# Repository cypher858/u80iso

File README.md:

# u80iso
tryna make a rama u80-a iso compatible. wish me luck.

LibreCAD was used to make the plate file

Started in KiCad 5.1.10, now in KiCad 7

I've been following the ai03 pcb design tutorial here https://wiki.ai03.com/books/pcb-design/chapter/pcb-designer-guide

currently in guide step 5 on building the pcb
https://wiki.ai03.com/books/pcb-design/page/pcb-guide-part-5---creating-the-pcb

in placing the controller and other circuit parts into the completed switch matrix, i noticed that what should be GND pins are reading as 5v instead. Bug? looking for feedback on this.

todo:
* fix above bug
* place jst connector footprint on the circuitboard
* tracing circuits
* silk screening for fun
* more? is there more?

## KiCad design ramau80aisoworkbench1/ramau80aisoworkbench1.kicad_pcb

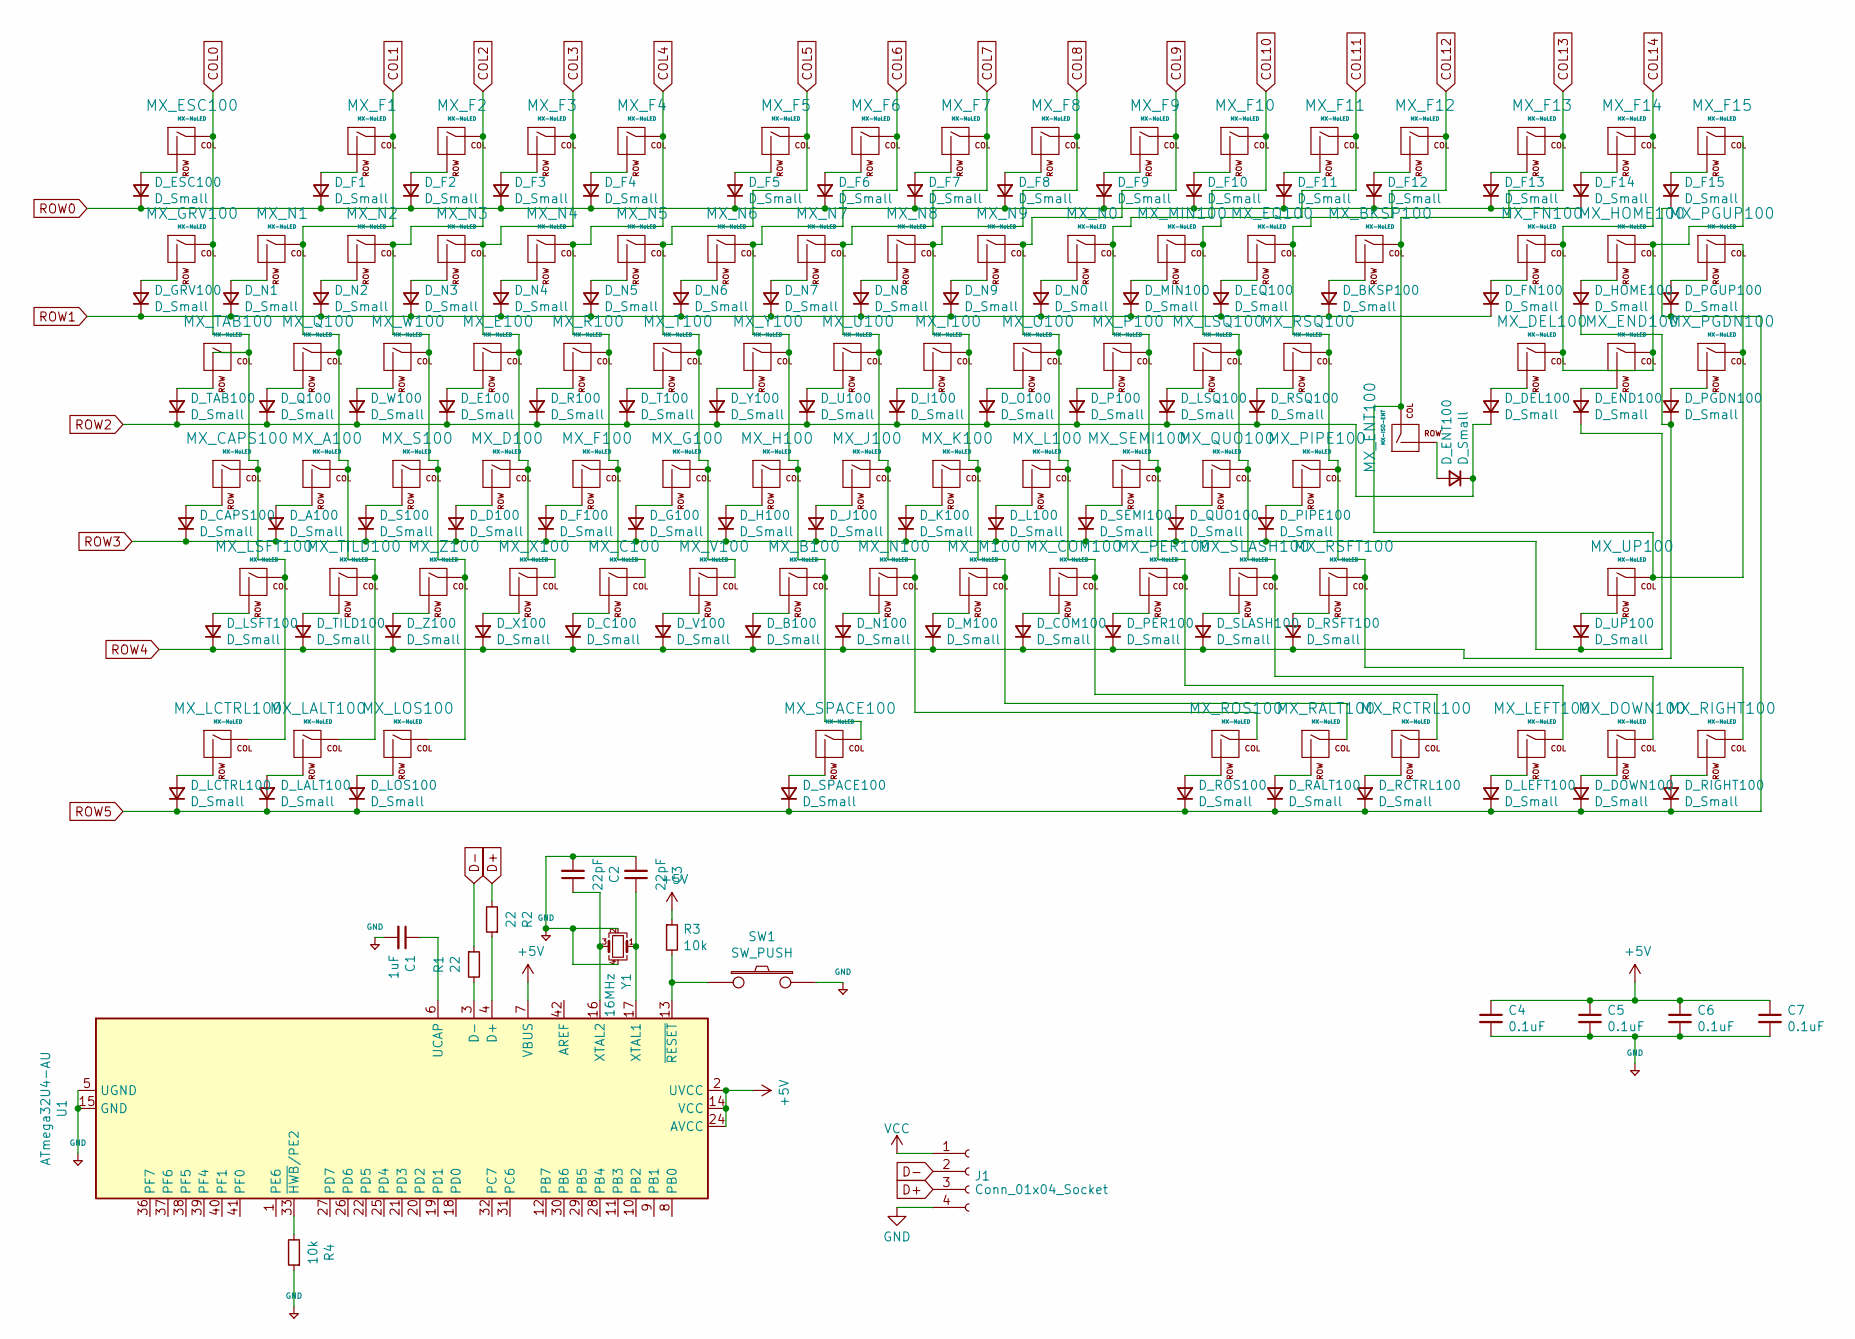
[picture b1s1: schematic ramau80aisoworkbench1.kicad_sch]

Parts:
C1: 1uF; C_0805_2012Metric
C2, C3: 22pF; C_0805_2012Metric
C4, C5, C6, C7: 0.1uF; C_0805_2012Metric
D_A100: D_Small; D_SOD-123
D_B100: D_Small; D_SOD-123
D_BKSP100: D_Small; D_SOD-123
D_C100: D_Small; D_SOD-123
D_CAPS100: D_Small; D_SOD-123
D_COM100: D_Small; D_SOD-123
D_D100: D_Small; D_SOD-123
D_DEL100: D_Small; D_SOD-123
D_DOWN100: D_Small; D_SOD-123
D_E100: D_Small; D_SOD-123
D_END100: D_Small; D_SOD-123
D_ENT100: D_Small; D_SOD-123
D_EQ100: D_Small; D_SOD-123
D_ESC100: D_Small; D_SOD-123
D_F1, D_F2, D_F3, D_F4, D_F5, D_F6, D_F7, D_F8, D_F9, D_F10, D_F11, D_F12, D_F13, D_F14, D_F15, D_F100: D_Small; D_SOD-123
D_FN100: D_Small; D_SOD-123
D_G100: D_Small; D_SOD-123
D_GRV100: D_Small; D_SOD-123
D_H100: D_Small; D_SOD-123
D_HOME100: D_Small; D_SOD-123
D_I100: D_Small; D_SOD-123
D_J100: D_Small; D_SOD-123
D_K100: D_Small; D_SOD-123
D_L100: D_Small; D_SOD-123
D_LALT100: D_Small; D_SOD-123
D_LCTRL100: D_Small; D_SOD-123
D_LEFT100: D_Small; D_SOD-123
D_LOS100: D_Small; D_SOD-123
D_LSFT100: D_Small; D_SOD-123
D_LSQ100: D_Small; D_SOD-123
D_M100: D_Small; D_SOD-123
D_MIN100: D_Small; D_SOD-123
D_N0, D_N1, D_N2, D_N3, D_N4, D_N5, D_N6, D_N7, D_N8, D_N9, D_N100: D_Small; D_SOD-123
D_O100: D_Small; D_SOD-123
D_P100: D_Small; D_SOD-123
D_PER100: D_Small; D_SOD-123
D_PGDN100: D_Small; D_SOD-123
D_PGUP100: D_Small; D_SOD-123
D_PIPE100: D_Small; D_SOD-123
D_Q100: D_Small; D_SOD-123
D_QUO100: D_Small; D_SOD-123
D_R100: D_Small; D_SOD-123
D_RALT100: D_Small; D_SOD-123
D_RCTRL100: D_Small; D_SOD-123
D_RIGHT100: D_Small; D_SOD-123
D_ROS100: D_Small; D_SOD-123
D_RSFT100: D_Small; D_SOD-123
D_RSQ100: D_Small; D_SOD-123
D_S100: D_Small; D_SOD-123
D_SEMI100: D_Small; D_SOD-123
D_SLASH100: D_Small; D_SOD-123
D_SPACE100: D_Small; D_SOD-123
D_T100: D_Small; D_SOD-123
D_TAB100: D_Small; D_SOD-123
D_TILD100: D_Small; D_SOD-123
D_U100: D_Small; D_SOD-123
D_UP100: D_Small; D_SOD-123
D_V100: D_Small; D_SOD-123
D_W100: D_Small; D_SOD-123
D_X100: D_Small; D_SOD-123
D_Y100: D_Small; D_SOD-123
D_Z100: D_Small; D_SOD-123
J1: Conn_01x04_Socket; JST_SH_SM04B-SRSS-TB_1x04-1MP_P1.00mm_Horizontal
MX_A100: MX-NoLED; MXOnly-1U-NoLED
MX_B100: MX-NoLED; MXOnly-1U-NoLED
MX_BKSP100: MX-NoLED; MXOnly-2U-NoLED
MX_C100: MX-NoLED; MXOnly-1U-NoLED
MX_CAPS100: MX-NoLED; MXOnly-1.75U-NoLED
MX_COM100: MX-NoLED; MXOnly-1U-NoLED
MX_D100: MX-NoLED; MXOnly-1U-NoLED
MX_DEL100: MX-NoLED; MXOnly-1U-NoLED
MX_DOWN100: MX-NoLED; MXOnly-1U-NoLED
MX_E100: MX-NoLED; MXOnly-1U-NoLED
MX_END100: MX-NoLED; MXOnly-1U-NoLED
MX_ENT100: MX-ISO-ENT; MXOnly-ISO-ROTATED-NoLED
MX_EQ100: MX-NoLED; MXOnly-1U-NoLED
MX_ESC100: MX-NoLED; MXOnly-1U-NoLED
MX_F1, MX_F2, MX_F3, MX_F4, MX_F5, MX_F6, MX_F7, MX_F8, MX_F9, MX_F10, MX_F11, MX_F12, MX_F13, MX_F14, MX_F15, MX_F100: MX-NoLED; MXOnly-1U-NoLED
MX_FN100: MX-NoLED; MXOnly-1U-NoLED
MX_G100: MX-NoLED; MXOnly-1U-NoLED
MX_GRV100: MX-NoLED; MXOnly-1U-NoLED
MX_H100: MX-NoLED; MXOnly-1U-NoLED
MX_HOME100: MX-NoLED; MXOnly-1U-NoLED
MX_I100: MX-NoLED; MXOnly-1U-NoLED
MX_J100: MX-NoLED; MXOnly-1U-NoLED
MX_K100: MX-NoLED; MXOnly-1U-NoLED
MX_L100: MX-NoLED; MXOnly-1U-NoLED
MX_LALT100: MX-NoLED; MXOnly-1U-NoLED
MX_LCTRL100: MX-NoLED; MXOnly-1.5U-NoLED
MX_LEFT100: MX-NoLED; MXOnly-1U-NoLED
MX_LOS100: MX-NoLED; MXOnly-1.5U-NoLED
MX_LSFT100: MX-NoLED; MXOnly-1.25U-NoLED
MX_LSQ100: MX-NoLED; MXOnly-1U-NoLED
MX_M100: MX-NoLED; MXOnly-1U-NoLED
MX_MIN100: MX-NoLED; MXOnly-1U-NoLED
MX_N0, MX_N1, MX_N2, MX_N3, MX_N4, MX_N5, MX_N6, MX_N7, MX_N8, MX_N9, MX_N100: MX-NoLED; MXOnly-1U-NoLED
MX_O100: MX-NoLED; MXOnly-1U-NoLED
MX_P100: MX-NoLED; MXOnly-1U-NoLED
MX_PER100: MX-NoLED; MXOnly-1U-NoLED
MX_PGDN100: MX-NoLED; MXOnly-1U-NoLED
MX_PGUP100: MX-NoLED; MXOnly-1U-NoLED
MX_PIPE100: MX-NoLED; MXOnly-1U-NoLED
MX_Q100: MX-NoLED; MXOnly-1U-NoLED
MX_QUO100: MX-NoLED; MXOnly-1U-NoLED
MX_R100: MX-NoLED; MXOnly-1U-NoLED
MX_RALT100: MX-NoLED; MXOnly-1U-NoLED
MX_RCTRL100: MX-NoLED; MXOnly-1.5U-NoLED
MX_RIGHT100: MX-NoLED; MXOnly-1U-NoLED
MX_ROS100: MX-NoLED; MXOnly-1.5U-NoLED
MX_RSFT100: MX-NoLED; MXOnly-2.75U-NoLED
MX_RSQ100: MX-NoLED; MXOnly-1U-NoLED
MX_S100: MX-NoLED; MXOnly-1U-NoLED
MX_SEMI100: MX-NoLED; MXOnly-1U-NoLED
MX_SLASH100: MX-NoLED; MXOnly-1U-NoLED
MX_SPACE100: MX-NoLED; MXOnly-7U-NoLED
MX_T100: MX-NoLED; MXOnly-1U-NoLED
MX_TAB100: MX-NoLED; MXOnly-1.5U-NoLED
MX_TILD100: MX-NoLED; MXOnly-1U-NoLED
MX_U100: MX-NoLED; MXOnly-1U-NoLED
MX_UP100: MX-NoLED; MXOnly-1U-NoLED
MX_V100: MX-NoLED; MXOnly-1U-NoLED
MX_W100: MX-NoLED; MXOnly-1U-NoLED
MX_X100: MX-NoLED; MXOnly-1U-NoLED
MX_Y100: MX-NoLED; MXOnly-1U-NoLED
MX_Z100: MX-NoLED; MXOnly-1U-NoLED
R1, R2: 22; R_0805_2012Metric
R3, R4: 10k; R_0805_2012Metric
SW1: SW_PUSH; PushButton_6x6mm_TH_Pretty
U1: ATmega32U4-AU; TQFP-44_10x10mm_P0.8mm
Y1: 16MHz; Crystal_SMD_3225-4Pin_3.2x2.5mm

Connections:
COL0: MX_CAPS100.1 (COL), MX_ESC100.1 (COL), MX_GRV100.1 (COL), MX_LCTRL100.1 (COL), MX_LSFT100.1 (COL), MX_TAB100.1 (COL)
COL1: MX_A100.1 (COL), MX_F1.1 (COL), MX_LALT100.1 (COL), MX_N1.1 (COL), MX_Q100.1 (COL), MX_TILD100.1 (COL)
COL2: MX_F2.1 (COL), MX_LOS100.1 (COL), MX_N2.1 (COL), MX_S100.1 (COL), MX_W100.1 (COL), MX_Z100.1 (COL)
COL3: MX_D100.1 (COL), MX_E100.1 (COL), MX_F3.1 (COL), MX_N3.1 (COL), MX_X100.1 (COL)
COL4: MX_C100.1 (COL), MX_F4.1 (COL), MX_F100.1 (COL), MX_N4.1 (COL), MX_R100.1 (COL)
COL5: MX_F5.1 (COL), MX_G100.1 (COL), MX_N5.1 (COL), MX_T100.1 (COL), MX_V100.1 (COL)
COL6: MX_B100.1 (COL), MX_F6.1 (COL), MX_H100.1 (COL), MX_N6.1 (COL), MX_SPACE100.1 (COL), MX_Y100.1 (COL)
COL7: MX_F7.1 (COL), MX_J100.1 (COL), MX_N7.1 (COL), MX_N100.1 (COL), MX_ROS100.1 (COL), MX_U100.1 (COL)
COL8: MX_F8.1 (COL), MX_I100.1 (COL), MX_K100.1 (COL), MX_M100.1 (COL), MX_N8.1 (COL), MX_RALT100.1 (COL)
COL9: MX_COM100.1 (COL), MX_F9.1 (COL), MX_L100.1 (COL), MX_N9.1 (COL), MX_O100.1 (COL), MX_RCTRL100.1 (COL)
COL10: MX_F10.1 (COL), MX_LEFT100.1 (COL), MX_N0.1 (COL), MX_P100.1 (COL), MX_PER100.1 (COL), MX_SEMI100.1 (COL)
COL11: MX_DOWN100.1 (COL), MX_F11.1 (COL), MX_LSQ100.1 (COL), MX_MIN100.1 (COL), MX_QUO100.1 (COL), MX_SLASH100.1 (COL)
COL12: MX_EQ100.1 (COL), MX_F12.1 (COL), MX_PIPE100.1 (COL), MX_RIGHT100.1 (COL), MX_RSFT100.1 (COL), MX_RSQ100.1 (COL)
COL13: MX_BKSP100.1 (COL), MX_ENT100.1 (COL), MX_F13.1 (COL), MX_PGDN100.1 (COL), MX_PGUP100.1 (COL), MX_UP100.1 (COL)
COL14: MX_DEL100.1 (COL), MX_END100.1 (COL), MX_F14.1 (COL), MX_F15.1 (COL), MX_FN100.1 (COL), MX_HOME100.1 (COL)
D+: J1.3, R2.2
D-: J1.2, R1.1
unnamed: D_A100.2 (A), MX_A100.2 (ROW)
unnamed: D_B100.2 (A), MX_B100.2 (ROW)
unnamed: D_BKSP100.2 (A), MX_BKSP100.2 (ROW)
unnamed: D_C100.2 (A), MX_C100.2 (ROW)
unnamed: D_CAPS100.2 (A), MX_CAPS100.2 (ROW)
unnamed: D_COM100.2 (A), MX_COM100.2 (ROW)
unnamed: D_D100.2 (A), MX_D100.2 (ROW)
unnamed: D_DEL100.2 (A), MX_DEL100.2 (ROW)
unnamed: D_DOWN100.2 (A), MX_DOWN100.2 (ROW)
unnamed: D_E100.2 (A), MX_E100.2 (ROW)
unnamed: D_END100.2 (A), MX_END100.2 (ROW)
unnamed: D_ENT100.2 (A), MX_ENT100.2 (ROW)
unnamed: D_EQ100.2 (A), MX_EQ100.2 (ROW)
unnamed: D_ESC100.2 (A), MX_ESC100.2 (ROW)
unnamed: D_F1.2 (A), MX_F1.2 (ROW)
unnamed: D_F2.2 (A), MX_F2.2 (ROW)
unnamed: D_F3.2 (A), MX_F3.2 (ROW)
unnamed: D_F4.2 (A), MX_F4.2 (ROW)
unnamed: D_F5.2 (A), MX_F5.2 (ROW)
unnamed: D_F6.2 (A), MX_F6.2 (ROW)
unnamed: D_F7.2 (A), MX_F7.2 (ROW)
unnamed: D_F8.2 (A), MX_F8.2 (ROW)
unnamed: D_F9.2 (A), MX_F9.2 (ROW)
unnamed: D_F10.2 (A), MX_F10.2 (ROW)
unnamed: D_F11.2 (A), MX_F11.2 (ROW)
unnamed: D_F12.2 (A), MX_F12.2 (ROW)
unnamed: D_F13.2 (A), MX_F13.2 (ROW)
unnamed: D_F14.2 (A), MX_F14.2 (ROW)
unnamed: D_F15.2 (A), MX_F15.2 (ROW)
unnamed: D_F100.2 (A), MX_F100.2 (ROW)
unnamed: D_FN100.2 (A), MX_FN100.2 (ROW)
unnamed: D_G100.2 (A), MX_G100.2 (ROW)
unnamed: D_GRV100.2 (A), MX_GRV100.2 (ROW)
unnamed: D_H100.2 (A), MX_H100.2 (ROW)
unnamed: D_HOME100.2 (A), MX_HOME100.2 (ROW)
unnamed: D_I100.2 (A), MX_I100.2 (ROW)
unnamed: D_J100.2 (A), MX_J100.2 (ROW)
unnamed: D_K100.2 (A), MX_K100.2 (ROW)
unnamed: D_L100.2 (A), MX_L100.2 (ROW)
unnamed: D_LALT100.2 (A), MX_LALT100.2 (ROW)
unnamed: D_LCTRL100.2 (A), MX_LCTRL100.2 (ROW)
unnamed: D_LEFT100.2 (A), MX_LEFT100.2 (ROW)
unnamed: D_LOS100.2 (A), MX_LOS100.2 (ROW)
unnamed: D_LSFT100.2 (A), MX_LSFT100.2 (ROW)
unnamed: D_LSQ100.2 (A), MX_LSQ100.2 (ROW)
unnamed: D_M100.2 (A), MX_M100.2 (ROW)
unnamed: D_MIN100.2 (A), MX_MIN100.2 (ROW)
unnamed: D_N0.2 (A), MX_N0.2 (ROW)
unnamed: D_N1.2 (A), MX_N1.2 (ROW)
unnamed: D_N2.2 (A), MX_N2.2 (ROW)
unnamed: D_N3.2 (A), MX_N3.2 (ROW)
unnamed: D_N4.2 (A), MX_N4.2 (ROW)
unnamed: D_N5.2 (A), MX_N5.2 (ROW)
unnamed: D_N6.2 (A), MX_N6.2 (ROW)
unnamed: D_N7.2 (A), MX_N7.2 (ROW)
unnamed: D_N8.2 (A), MX_N8.2 (ROW)
unnamed: D_N9.2 (A), MX_N9.2 (ROW)
unnamed: D_N100.2 (A), MX_N100.2 (ROW)
unnamed: D_O100.2 (A), MX_O100.2 (ROW)
unnamed: D_P100.2 (A), MX_P100.2 (ROW)
unnamed: D_PER100.2 (A), MX_PER100.2 (ROW)
unnamed: D_PGDN100.2 (A), MX_PGDN100.2 (ROW)
unnamed: D_PGUP100.2 (A), MX_PGUP100.2 (ROW)
unnamed: D_PIPE100.2 (A), MX_PIPE100.2 (ROW)
unnamed: D_Q100.2 (A), MX_Q100.2 (ROW)
unnamed: D_QUO100.2 (A), MX_QUO100.2 (ROW)
unnamed: D_R100.2 (A), MX_R100.2 (ROW)
unnamed: D_RALT100.2 (A), MX_RALT100.2 (ROW)
unnamed: D_RCTRL100.2 (A), MX_RCTRL100.2 (ROW)
unnamed: D_RIGHT100.2 (A), MX_RIGHT100.2 (ROW)
unnamed: D_ROS100.2 (A), MX_ROS100.2 (ROW)
unnamed: D_RSFT100.2 (A), MX_RSFT100.2 (ROW)
unnamed: D_RSQ100.2 (A), MX_RSQ100.2 (ROW)
unnamed: D_S100.2 (A), MX_S100.2 (ROW)
unnamed: D_SEMI100.2 (A), MX_SEMI100.2 (ROW)
unnamed: D_SLASH100.2 (A), MX_SLASH100.2 (ROW)
unnamed: D_SPACE100.2 (A), MX_SPACE100.2 (ROW)
unnamed: D_T100.2 (A), MX_T100.2 (ROW)
unnamed: D_TAB100.2 (A), MX_TAB100.2 (ROW)
unnamed: D_TILD100.2 (A), MX_TILD100.2 (ROW)
unnamed: D_U100.2 (A), MX_U100.2 (ROW)
unnamed: D_UP100.2 (A), MX_UP100.2 (ROW)
unnamed: D_V100.2 (A), MX_V100.2 (ROW)
unnamed: D_W100.2 (A), MX_W100.2 (ROW)
unnamed: D_X100.2 (A), MX_X100.2 (ROW)
unnamed: D_Y100.2 (A), MX_Y100.2 (ROW)
unnamed: D_Z100.2 (A), MX_Z100.2 (ROW)
unnamed: R2.1, U1.4 (D+)
unnamed: R1.2, U1.3 (D-)
unnamed: C1.1, U1.6 (UCAP)
unnamed: C3.1, U1.17 (XTAL1), Y1.1
unnamed: C2.1, U1.16 (XTAL2), Y1.3
unnamed: R4.2, U1.33 (~HWB/PE2)
unnamed: R3.2, SW1.1, U1.13 (~RESET)
ROW0: D_ESC100.1 (K), D_F1.1 (K), D_F2.1 (K), D_F3.1 (K), D_F4.1 (K), D_F5.1 (K), D_F6.1 (K), D_F7.1 (K), D_F8.1 (K), D_F9.1 (K), D_F10.1 (K), D_F11.1 (K), D_F12.1 (K), D_F13.1 (K), D_F14.1 (K)
ROW1: D_BKSP100.1 (K), D_EQ100.1 (K), D_FN100.1 (K), D_GRV100.1 (K), D_MIN100.1 (K), D_N0.1 (K), D_N1.1 (K), D_N2.1 (K), D_N3.1 (K), D_N4.1 (K), D_N5.1 (K), D_N6.1 (K), D_N7.1 (K), D_N8.1 (K), D_N9.1 (K)
ROW2: D_DEL100.1 (K), D_E100.1 (K), D_ENT100.1 (K), D_I100.1 (K), D_LSQ100.1 (K), D_O100.1 (K), D_P100.1 (K), D_Q100.1 (K), D_R100.1 (K), D_RSQ100.1 (K), D_T100.1 (K), D_TAB100.1 (K), D_U100.1 (K), D_W100.1 (K), D_Y100.1 (K)
ROW3: D_A100.1 (K), D_CAPS100.1 (K), D_D100.1 (K), D_END100.1 (K), D_F100.1 (K), D_G100.1 (K), D_H100.1 (K), D_J100.1 (K), D_K100.1 (K), D_L100.1 (K), D_PIPE100.1 (K), D_QUO100.1 (K), D_S100.1 (K), D_SEMI100.1 (K), D_UP100.1 (K)
ROW4: D_B100.1 (K), D_C100.1 (K), D_COM100.1 (K), D_HOME100.1 (K), D_LSFT100.1 (K), D_M100.1 (K), D_N100.1 (K), D_PER100.1 (K), D_PGDN100.1 (K), D_RSFT100.1 (K), D_SLASH100.1 (K), D_TILD100.1 (K), D_V100.1 (K), D_X100.1 (K), D_Z100.1 (K)
ROW5: D_DOWN100.1 (K), D_F15.1 (K), D_LALT100.1 (K), D_LCTRL100.1 (K), D_LEFT100.1 (K), D_LOS100.1 (K), D_PGUP100.1 (K), D_RALT100.1 (K), D_RCTRL100.1 (K), D_RIGHT100.1 (K), D_ROS100.1 (K), D_SPACE100.1 (K)
VCC: J1.1; also elsewhere on the board

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
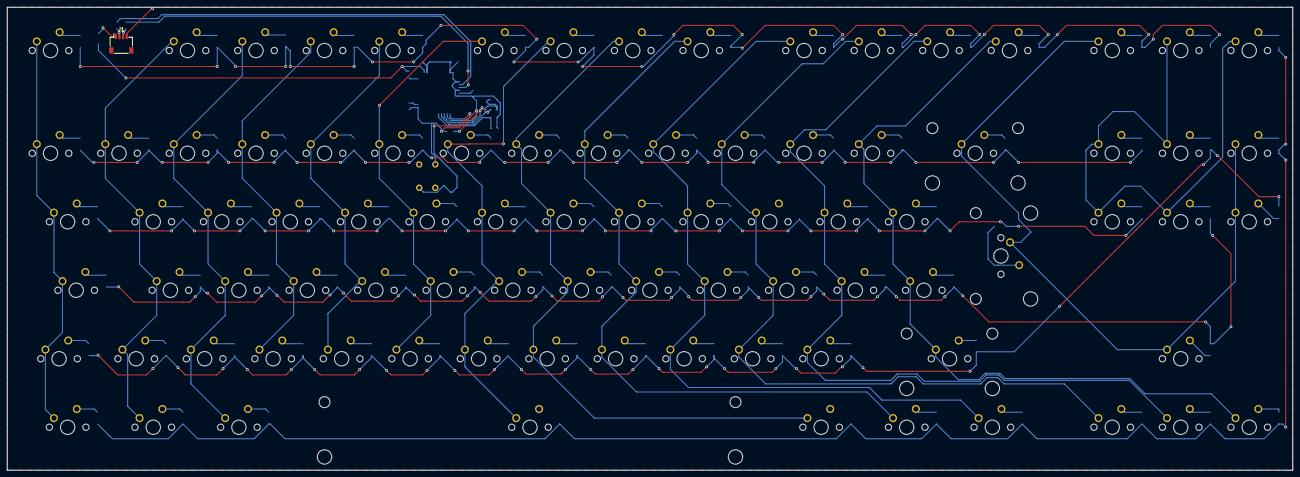
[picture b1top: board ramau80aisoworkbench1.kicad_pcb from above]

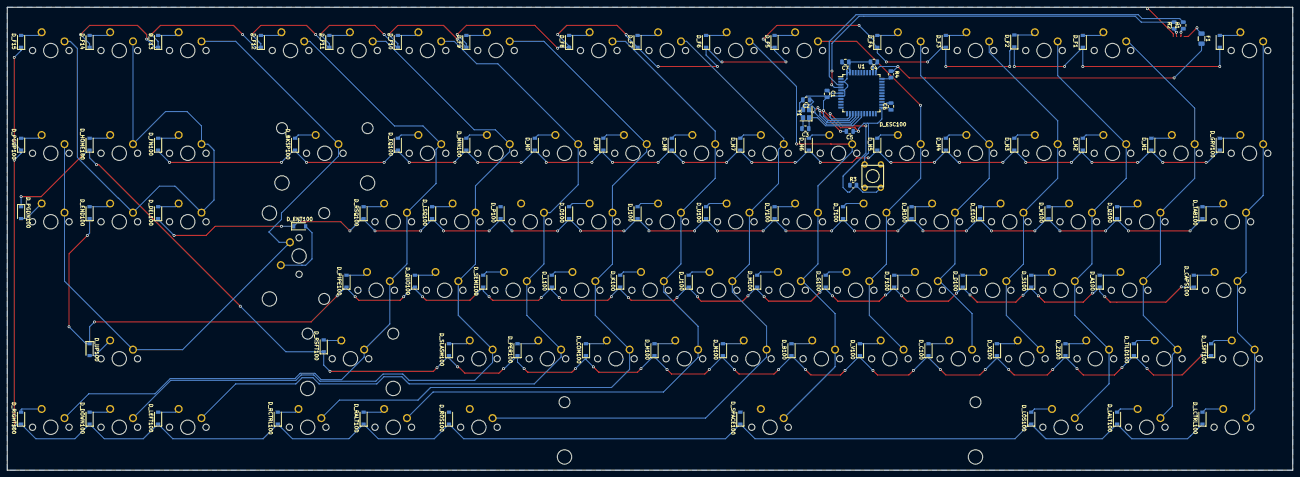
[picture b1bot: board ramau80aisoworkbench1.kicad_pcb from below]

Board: 2 copper layers, 357.5 x 128.8 mm, 190 parts (102 on the bottom side), 119 nets.

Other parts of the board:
F1: 500mA; Fuse_1206_3216Metric

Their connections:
VCC: F1.1; also elsewhere on the board

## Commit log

2023-03-15 pushing work so far
    contains several files.
2023-03-15 adding submodules
2023-03-15 updated libraries for both files
2023-03-15 starting schematic over following ai03 instructions... lets see. todo, turn usb mini-b into usb-c later...
2023-03-15 grid complete. probs need more capacitors.
2023-03-15 label updates
2023-03-15 mx footprints now sit in proper spots for u80
2023-03-15 diodes aligned to switches
2023-03-15 fixed error in footprint assignment. updated switch footprints to use appropriate size, ditched leds
2023-03-15 adding plate file to repo
2023-03-16 re-aligned spacebar. wups.
2023-03-16 lee. updated to kicad 7. adding usbc library
2023-03-16 added 4 pin to schematic. WHAT JST FOOTPRINT DO I USE?
2023-03-16 all parts on board! lets make sure the resistors and capacitors are all right and that the ground issue is sorted. then routing
2023-06-27 added traces
2023-06-27 more traces
